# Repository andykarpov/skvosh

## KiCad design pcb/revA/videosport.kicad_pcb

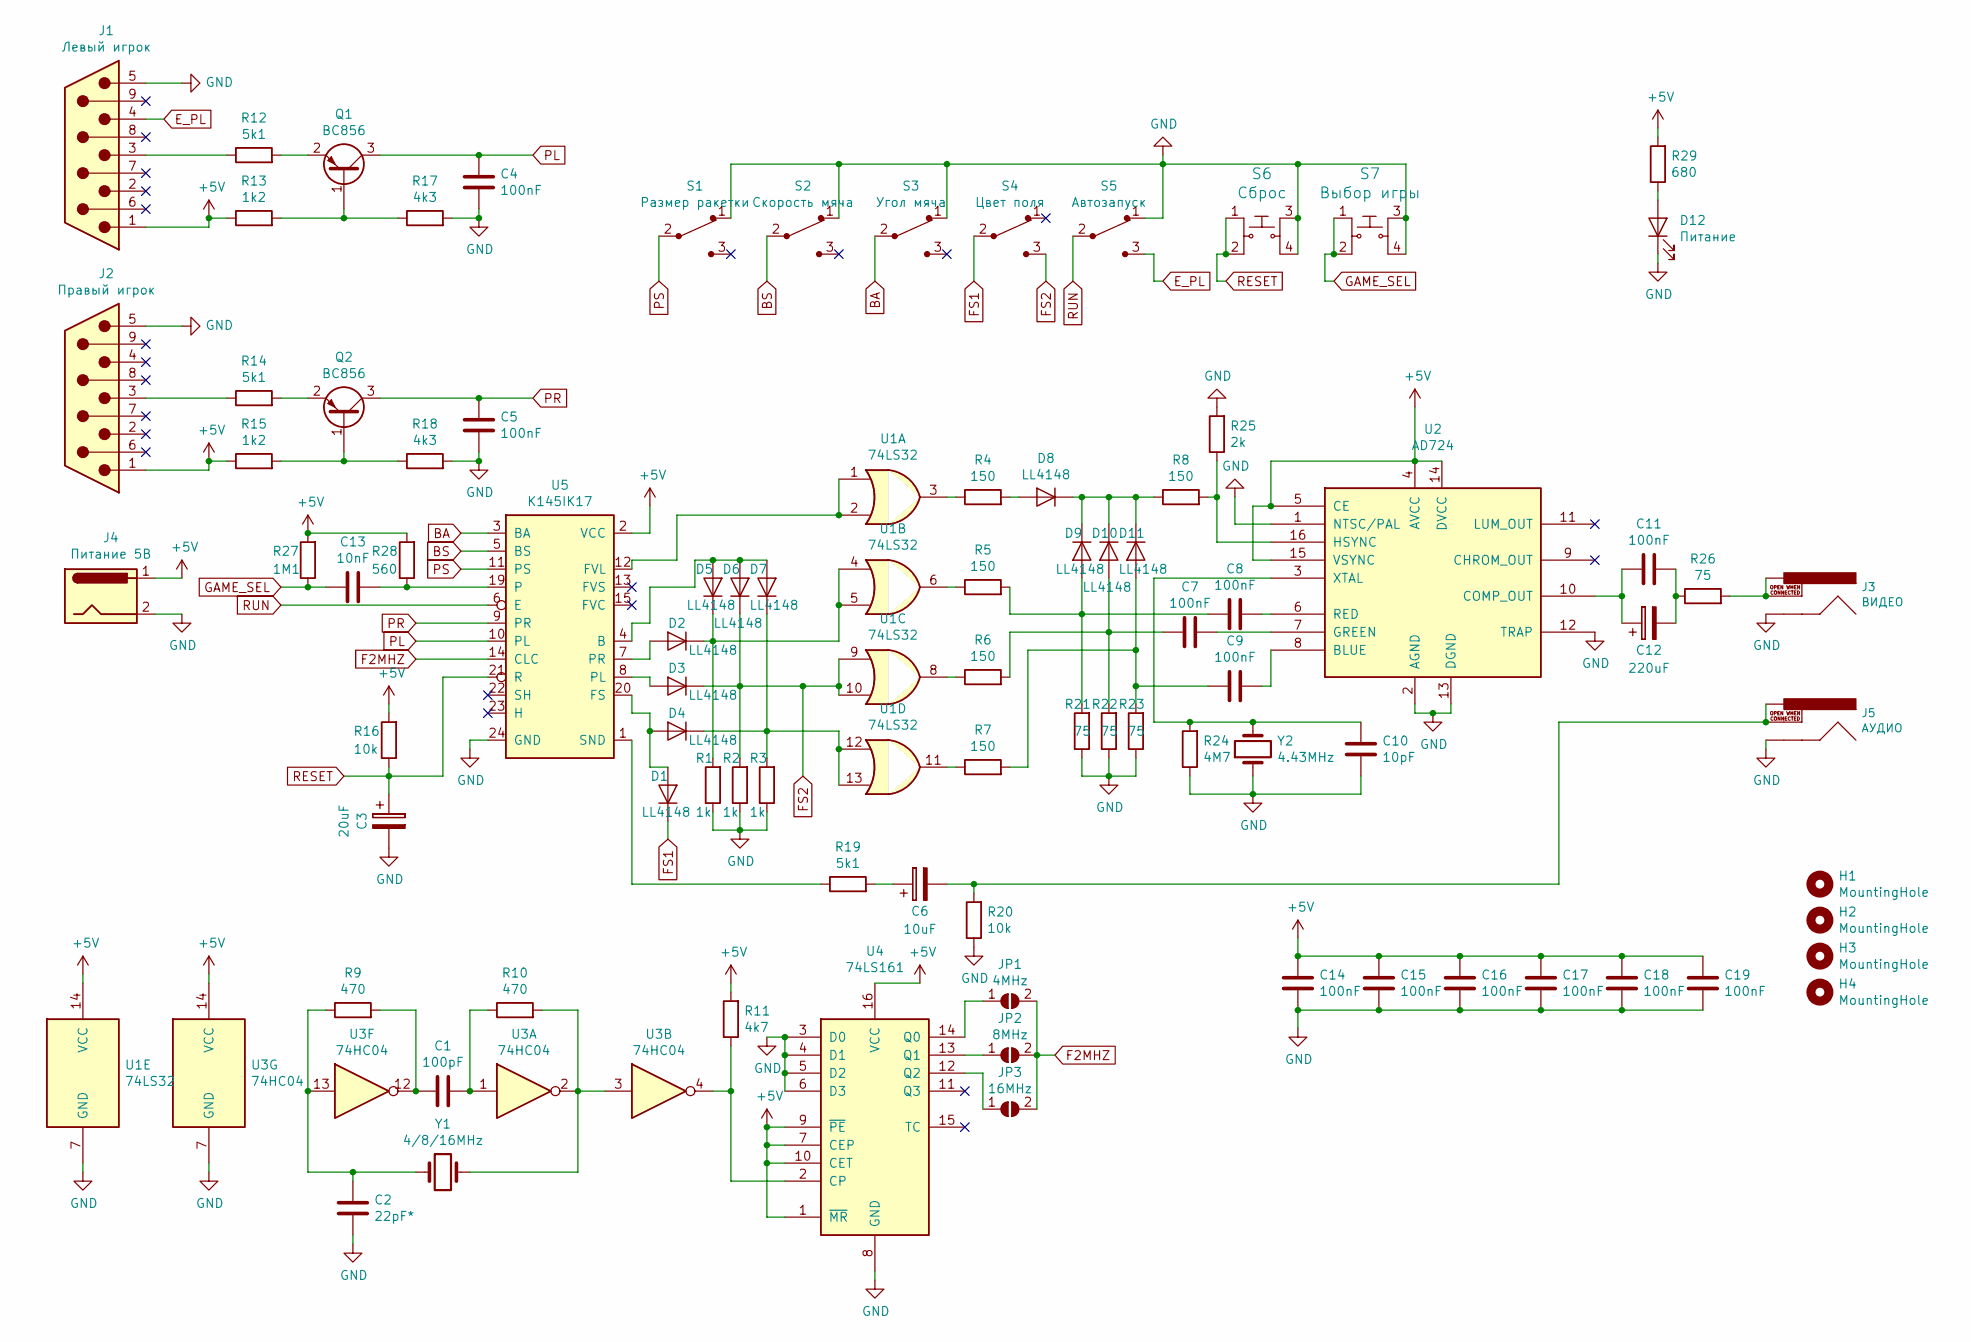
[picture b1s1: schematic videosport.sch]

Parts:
C1: 100pF; 0805
C2: 22pF*; 0805
C3: 20uF; CP_EIA-6032-28_Kemet-C_Pad2.25x2.35mm_HandSolder
C4, C5, C7, C8, C9, C11, C14, C15, C16, C17, C18, C19: 100nF; 0805
C6: 10uF; CP_EIA-6032-28_Kemet-C_Pad2.25x2.35mm_HandSolder
C10: 10pF; 0805
C12: 220uF; CP_EIA-7343-31_Kemet-D_Pad2.25x2.55mm_HandSolder
C13: 10nF; 0805
D1, D2, D3, D4, D5, D6, D7, D8, D9, D10, D11: LL4148; D_MiniMELF
D12: Питание; LED_1206_3216Metric_Pad1.42x1.75mm_HandSolder
H1, H2, H3, H4: MountingHole; MountingHole_3.2mm_M3_Pad_Via
J1: Левый игрок; DSUB-9_Male_Horizontal_P2.77x2.84mm_EdgePinOffset4.94mm_Hou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
J2: Правый игрок; DSUB-9_Male_Horizontal_P2.77x2.84mm_EdgePinOffset4.94mm_Hou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
J3: ВИДЕО; RCA
J4: Питание 5В; BarrelJack_Wuerth_6941xx301002
J5: АУДИО; RCA
JP1: 4MHz; SolderJumper-2_P1.3mm_Open_TrianglePad1.0x1.5mm
JP2: 8MHz; SolderJumper-2_P1.3mm_Open_TrianglePad1.0x1.5mm
JP3: 16MHz; SolderJumper-2_P1.3mm_Open_TrianglePad1.0x1.5mm
Q1, Q2: BC856; SOT-23
R1, R2, R3: 1k; 0805
R4, R5, R6, R7, R8: 150; 0805
R9, R10: 470; 0805
R11: 4k7; 0805
R12, R14, R19: 5k1; 0805
R13, R15: 1k2; 0805
R16, R20: 10k; 0805
R17, R18: 4k3; 0805
R21, R22, R23, R26: 75; 0805
R24: 4M7; 0805
R25: 2k; 0805
R27: 1M1; 0805
R28: 560; 0805
R29: 680; 0805
S1: Размер ракетки; Switch_Slide_11.6x4mm_EG1218; MPN EG1218; Digi-Key_PN EG1903-ND
S2: Скорость мяча; Switch_Slide_11.6x4mm_EG1218; MPN EG1218; Digi-Key_PN EG1903-ND
S3: Угол мяча; Switch_Slide_11.6x4mm_EG1218; MPN EG1218; Digi-Key_PN EG1903-ND
S4: Цвет поля; Switch_Slide_11.6x4mm_EG1218; MPN EG1218; Digi-Key_PN EG1903-ND
S5: Автозапуск; Switch_Slide_11.6x4mm_EG1218; MPN EG1218; Digi-Key_PN EG1903-ND
S6: Сброс; Switch_Tactile_THT_6x6mm; MPN 1825910-6; Digi-Key_PN 450-1650-ND
S7: Выбор игры; Switch_Tactile_THT_6x6mm; MPN 1825910-6; Digi-Key_PN 450-1650-ND
U1: 74LS32; SOIC-14_3.9x8.7mm_P1.27mm
U2: AD724; SOIC-16W_7.5x10.3mm_P1.27mm
U3: 74HC04; SOIC-14_3.9x8.7mm_P1.27mm
U4: 74LS161; SOIC-16_3.9x9.9mm_P1.27mm
U5: K145IK17; DIP-24_W15.24mm
Y1: 4/8/16MHz; Crystal_HC49-U_Vertical
Y2: 4.43MHz; Crystal_HC49-U_Vertical

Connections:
+5V: C14.2, C15.2, C16.2, C17.2, C18.2, C19.2, J1.1, J2.1, J4.1, R11.2, R13.1, R15.1, R16.2, R27.2, R28.2, R29.2, U1.14 (VCC), U2.4 (AVCC), U2.5 (CE), U2.14 (DVCC), U2.15 (VSYNC), U3.14 (VCC), U4.1 (~MR), U4.7 (CEP), U4.9 (~PE), U4.10 (CET), U4.16 (VCC), U5.2 (VCC)
BA: S3.2, U5.3 (BA)
BS: S2.2, U5.5 (BS)
E_PL: J1.4, S5.3
F2MHZ: JP1.2 (B), JP2.2 (B), JP3.2 (B), U5.14 (CLC)
FS1: D1.1 (K), S4.2
FS2: D3.1 (K), D6.1 (K), R2.2, S4.3, U1.9, U1.10
GAME_SEL: C13.1, R27.1, S7.1, S7.2
GND: C2.1, C3.2, C4.1, C5.1, C10.1, C14.1, C15.1, C16.1, C17.1, C18.1, C19.1, D12.1 (K), J1.5, J2.5, J3.SHEL (SHELL), J4.2, J5.SHEL (SHELL), R1.1, R2.1, R3.1, R17.2, R18.2, R20.1, R21.1, R22.1, R23.1, R24.1, R25.2, S1.1, S2.1, S3.1, S5.1, S6.3, S6.4, S7.3, S7.4, U1.7 (GND), U2.1 (NTSC/PAL), U2.2 (AGND), U2.12 (TRAP), U2.13 (DGND), U3.7 (GND), U4.3 (D0), U4.4 (D1), U4.5 (D2), U4.6 (D3), U4.8 (GND), U5.24 (GND), Y2.1
unnamed: C1.1, R9.2, U3.12
unnamed: C1.2, R10.1, U3.1
unnamed: C2.2, R9.1, U3.13, Y1.1
unnamed: C6.1, R19.2
unnamed: C6.2, J5.PIN, J5.SWIT (SWITCH), R20.2
unnamed: C7.1, D10.2 (A), R6.2, R22.2
unnamed: C7.2, U2.7 (GREEN)
unnamed: C8.1, D9.2 (A), R5.2, R21.2
unnamed: C8.2, U2.6 (RED)
unnamed: C9.1, D11.2 (A), R7.2, R23.2
unnamed: C9.2, U2.8 (BLUE)
unnamed: C10.2, R24.2, U2.3 (XTAL), Y2.2
unnamed: C11.1, C12.1, U2.10 (COMP_OUT)
unnamed: C11.2, C12.2, R26.1
unnamed: C13.2, R28.1, U5.19
unnamed: D1.2 (A), D4.2 (A), U5.20 (FS)
unnamed: D2.1 (K), D5.1 (K), R1.2, U1.4, U1.5
unnamed: D2.2 (A), U5.7 (PR)
unnamed: D3.2 (A), U5.8 (PL)
unnamed: D4.1 (K), D7.1 (K), R3.2, U1.12, U1.13
unnamed: D5.2 (A), D6.2 (A), D7.2 (A), U5.4 (B)
unnamed: D8.2 (A), R4.2
unnamed: D8.1 (K), D9.1 (K), D10.1 (K), D11.1 (K), R8.1
unnamed: D12.2 (A), R29.1
unnamed: J1.3, R12.1
unnamed: J2.3, R14.1
unnamed: J3.PIN, J3.SWIT (SWITCH), R26.2
unnamed: JP1.1 (A), U4.14 (Q0)
unnamed: JP2.1 (A), U4.13 (Q1)
unnamed: JP3.1 (A), U4.12 (Q2)
unnamed: Q1.1 (B), R13.2, R17.1
unnamed: Q1.2 (E), R12.2
unnamed: Q2.1 (B), R15.2, R18.1
unnamed: Q2.2 (E), R14.2
unnamed: R4.1, U1.3
unnamed: R5.1, U1.6
unnamed: R6.1, U1.8
unnamed: R7.1, U1.11
unnamed: R10.2, U3.2, U3.3, Y1.2
unnamed: R11.1, U3.4, U4.2 (CP)
unnamed: R19.1, U5.1 (SND)
unnamed: R8.2, R25.1, U2.16 (HSYNC)
unnamed: U1.1, U1.2, U5.12 (FVL)
PL: C4.2, Q1.3 (C), U5.10 (PL)
PR: C5.2, Q2.3 (C), U5.9 (PR)
PS: S1.2, U5.11 (PS)
RESET: C3.1, R16.1, S6.1, S6.2, U5.21 (R)
RUN: S5.2, U5.6 (E)

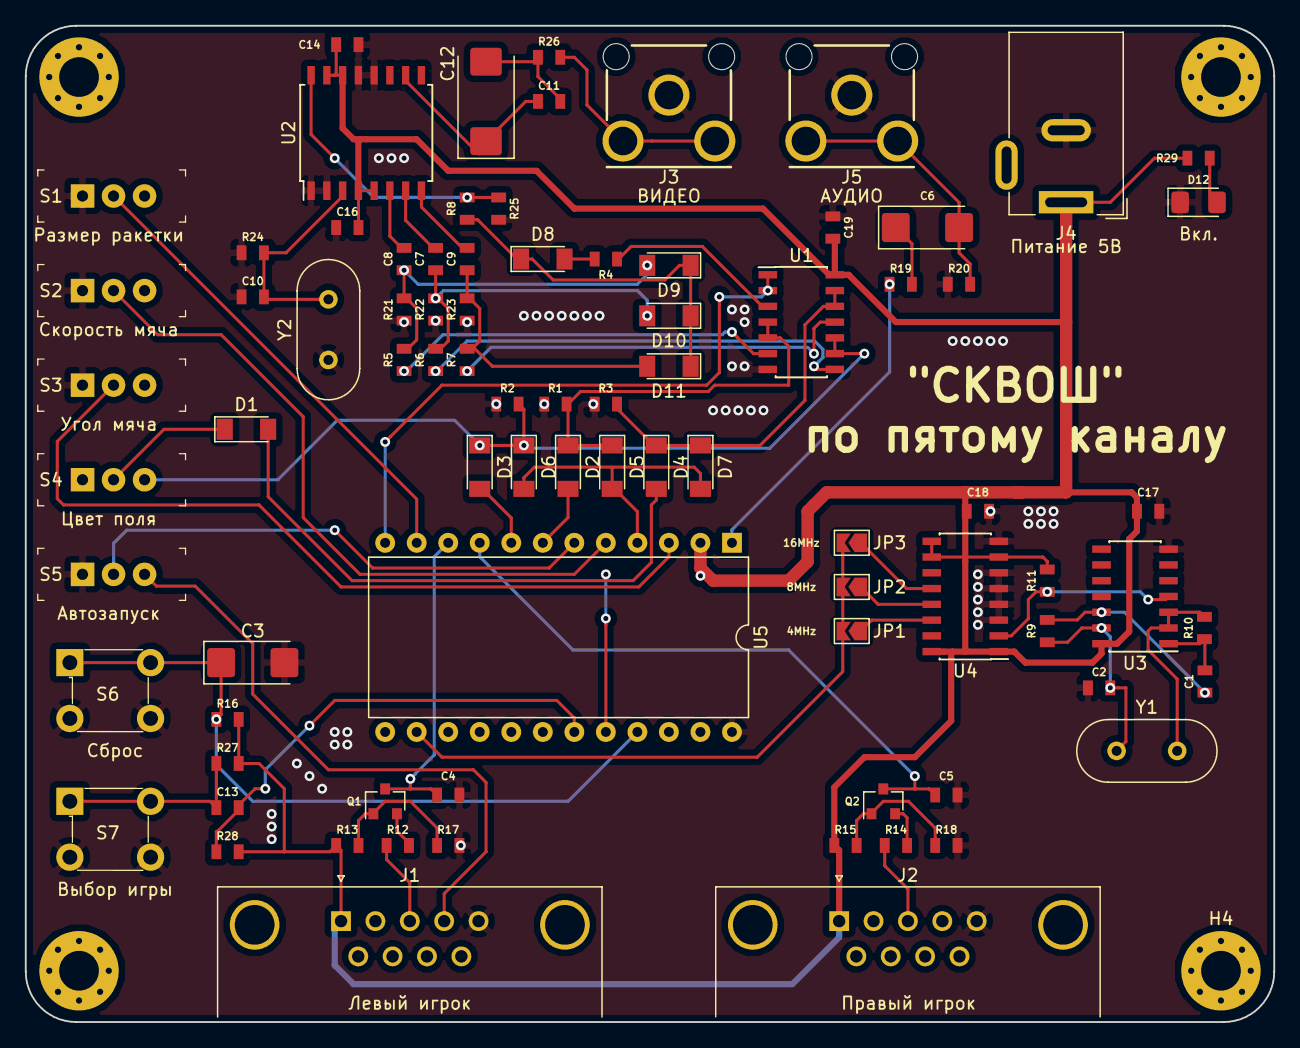
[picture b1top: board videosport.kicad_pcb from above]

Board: 2 copper layers, 100.6 x 80.3 mm, 88 parts (1 on the bottom side), 57 nets.

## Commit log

2020-01-13 pcb rev.B
